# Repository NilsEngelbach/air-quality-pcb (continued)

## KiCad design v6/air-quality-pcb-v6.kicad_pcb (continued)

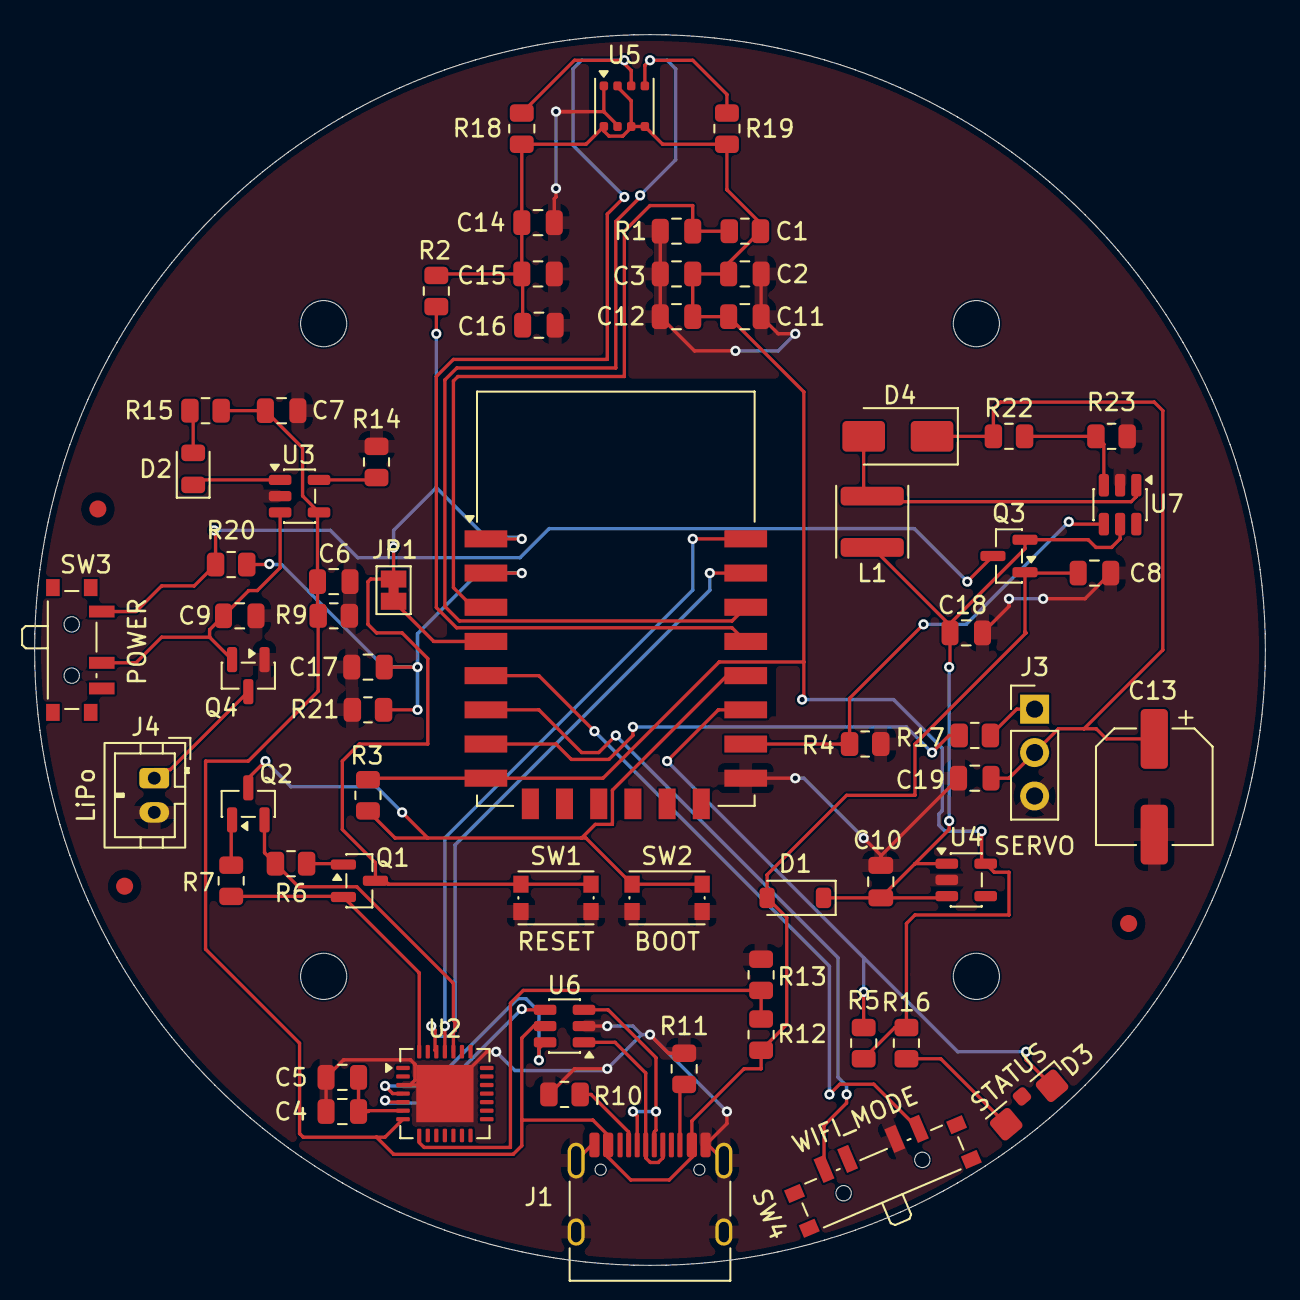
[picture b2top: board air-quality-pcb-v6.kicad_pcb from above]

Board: 2 copper layers, 72.0 x 72.0 mm, 72 parts (0 on the bottom side), 41 nets.

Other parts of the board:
FID1, FID2, FID3: Fiducial; Fiducial_1mm_Mask2mm
H1, H2, H3, H4: M2.5; MountingHole_2.7mm_M2.5

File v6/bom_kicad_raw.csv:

"Reference","Value","Footprint","Manufacturer","MPN","Description"
"C1","100nF","Capacitor_SMD:C_0805_2012Metric","Samsung Electro-Mechanics","CL21B104KBCNNNC","CAP CER 0.1UF 50V X7R 0805"
"C2","10uF","Capacitor_SMD:C_0805_2012Metric","YAGEO","CC0805KRX5R7BB106","CAP CER 10UF 16V X5R 0805"
"C3","100nF","Capacitor_SMD:C_0805_2012Metric","Samsung Electro-Mechanics","CL21B104KBCNNNC","CAP CER 0.1UF 50V X7R 0805"
"C4","4.7uF","Capacitor_SMD:C_0805_2012Metric","Samsung Electro-Mechanics","CL21A475KOFNNNG","CAP CER 4.7UF 16V X5R 0805"
"C5","100nF","Capacitor_SMD:C_0805_2012Metric","Samsung Electro-Mechanics","CL21B104KBCNNNC","CAP CER 0.1UF 50V X7R 0805"
"C6","4.7uF","Capacitor_SMD:C_0805_2012Metric","Samsung Electro-Mechanics","CL21A475KOFNNNG","CAP CER 4.7UF 16V X5R 0805"
"C7","4.7uF","Capacitor_SMD:C_0805_2012Metric","Samsung Electro-Mechanics","CL21A475KOFNNNG","CAP CER 4.7UF 16V X5R 0805"
"C8","100nF","Capacitor_SMD:C_0805_2012Metric","Samsung Electro-Mechanics","CL21B104KBCNNNC","CAP CER 0.1UF 50V X7R 0805"
"C9","4.7uF","Capacitor_SMD:C_0805_2012Metric","Samsung Electro-Mechanics","CL21A475KOFNNNG","CAP CER 4.7UF 16V X5R 0805"
"C10","1uF","Capacitor_SMD:C_0805_2012Metric","Samsung Electro-Mechanics","CL21B105KOFNNWE","CAP CER 1UF 16V X7R 0805"
"C11","10uF","Capacitor_SMD:C_0805_2012Metric","YAGEO","CC0805KRX5R7BB106","CAP CER 10UF 16V X5R 0805"
"C12","100nF","Capacitor_SMD:C_0805_2012Metric","Samsung Electro-Mechanics","CL21B104KBCNNNC","CAP CER 0.1UF 50V X7R 0805"
"C13","100uF","Capacitor_SMD:CP_Elec_6.3x5.4","Nichicon","UCD1C101MCL1GS","CAP ALUM 100UF 20% 16V SMD 6.3mm dia"
"C14","100nF","Capacitor_SMD:C_0805_2012Metric","Samsung Electro-Mechanics","CL21B104KBCNNNC","CAP CER 0.1UF 50V X7R 0805"
"C15","100nF","Capacitor_SMD:C_0805_2012Metric","Samsung Electro-Mechanics","CL21B104KBCNNNC","CAP CER 0.1UF 50V X7R 0805"
"C16","10uF","Capacitor_SMD:C_0805_2012Metric","YAGEO","CC0805KRX5R7BB106","CAP CER 10UF 16V X5R 0805"
"C17","100nF","Capacitor_SMD:C_0805_2012Metric","Samsung Electro-Mechanics","CL21B104KBCNNNC","CAP CER 0.1UF 50V X7R 0805"
"C18","10uF","Capacitor_SMD:C_0805_2012Metric","YAGEO","CC0805KRX5R7BB106","CAP CER 10UF 16V X5R 0805"
"C19","22uF","Capacitor_SMD:C_0805_2012Metric","Samsung Electro-Mechanics","CL21A226KOQNNNG","CAP CER 22UF 16V X5R 0805"
"D1","B5819W","Diode_SMD:D_SOD-123","MCC (Micro Commercial Components)","B5819W-TP","DIODE SCHOTTKY 40V 1A SOD-123"
"D2","CHG-GREEN","LED_SMD:LED_0805_2012Metric","Lite-On Inc.","LTST-C170GKT","LED GREEN CLEAR 0805 SMD"
"D3","STATUS","LED_SMD:LED_Kingbright_KPA-3010_3x2x1mm","Kingbright","KPA-3010QBC-D","LED BLUE CLEAR RIGHT ANGLE SMD 3.0x2.0x1.0mm side-view; status + WiFi setup feedback"
"D4","SS34","Diode_SMD:D_SMA","Comchip Technology","SS34-HF","DIODE SCHOTTKY 40V 3A DO-214AC (SMA)"
"J1","USB-C","Connector_USB:USB_C_Receptacle_HRO_TYPE-C-31-M-12","Korean Hroparts (HRO)","TYPE-C-31-M-12","USB Type-C 2.0 receptacle 16P mid-mount SMD"
"J3","SERVO","Connector_PinHeader_2.54mm:PinHeader_1x03_P2.54mm_Vertical","Wurth Elektronik","61300311121","CONN HEADER VERT 3POS 2.54MM THT"
"J4","LiPo","Connector_JST:JST_PH_B2B-PH-K_1x02_P2.00mm_Vertical","JST","B2B-PH-K-S","CONN HEADER VERT 2POS 2MM JST PH THT"
"JP1","DEEPSLEEP","Jumper:SolderJumper-2_P1.3mm_Bridged_Pad1.0x1.5mm","","",""
"L1","10uH","Inductor_SMD:L_Sunlord_SWPA4030S","Sunlord","SWPA4030S100MT","FIXED IND 10UH 1.5A 130 MOHM SMD 4x4x3"
"Q1","MMBT2222A","Package_TO_SOT_SMD:SOT-23","onsemi","MMBT2222ALT1G","TRANS NPN 40V 0.6A SOT-23"
"Q2","MMBT2222A","Package_TO_SOT_SMD:SOT-23","onsemi","MMBT2222ALT1G","TRANS NPN 40V 0.6A SOT-23"
"Q3","DMG2305UX","Package_TO_SOT_SMD:SOT-23","Diodes Incorporated","DMG2305UX-7","MOSFET P-CH 20V 4.2A SOT-23"
"Q4","DMG2305UX","Package_TO_SOT_SMD:SOT-23","Diodes Incorporated","DMG2305UX-7","MOSFET P-CH 20V 4.2A SOT-23"
"R1","10k","Resistor_SMD:R_0805_2012Metric","YAGEO","RC0805FR-0710KL","RES 10K OHM 1% 1/8W 0805"
"R2","10k","Resistor_SMD:R_0805_2012Metric","YAGEO","RC0805FR-0710KL","RES 10K OHM 1% 1/8W 0805"
"R3","10k","Resistor_SMD:R_0805_2012Metric","YAGEO","RC0805FR-0710KL","RES 10K OHM 1% 1/8W 0805"
"R4","10k","Resistor_SMD:R_0805_2012Metric","YAGEO","RC0805FR-0710KL","RES 10K OHM 1% 1/8W 0805"
"R5","10k","Resistor_SMD:R_0805_2012Metric","YAGEO","RC0805FR-0710KL","RES 10K OHM 1% 1/8W 0805"
"R6","10k","Resistor_SMD:R_0805_2012Metric","YAGEO","RC0805FR-0710KL","RES 10K OHM 1% 1/8W 0805"
"R7","10k","Resistor_SMD:R_0805_2012Metric","YAGEO","RC0805FR-0710KL","RES 10K OHM 1% 1/8W 0805"
"R9","100k","Resistor_SMD:R_0805_2012Metric","YAGEO","RC0805FR-07100KL","RES 100K OHM 1% 1/8W 0805"
"R10","5.1k","Resistor_SMD:R_0805_2012Metric","YAGEO","RC0805FR-075K1L","RES 5.1K OHM 1% 1/8W 0805"
"R11","5.1k","Resistor_SMD:R_0805_2012Metric","YAGEO","RC0805FR-075K1L","RES 5.1K OHM 1% 1/8W 0805"
"R12","22.1k","Resistor_SMD:R_0805_2012Metric","YAGEO","RC0805FR-0722K1L","RES 22.1K OHM 1% 1/8W 0805"
"R13","47.5k","Resistor_SMD:R_0805_2012Metric","YAGEO","RC0805FR-0747K5L","RES 47.5K OHM 1% 1/8W 0805"
"R14","2.2k","Resistor_SMD:R_0805_2012Metric","YAGEO","RC0805FR-072K2L","RES 2.2K OHM 1% 1/8W 0805"
"R15","1k","Resistor_SMD:R_0805_2012Metric","YAGEO","RC0805FR-071KL","RES 1K OHM 1% 1/8W 0805"
"R16","220R","Resistor_SMD:R_0805_2012Metric","YAGEO","RC0805FR-07220RL","RES 220 OHM 1% 1/8W 0805"
"R17","100R","Resistor_SMD:R_0805_2012Metric","YAGEO","RC0805FR-07100RL","RES 100 OHM 1% 1/8W 0805"
"R18","10k","Resistor_SMD:R_0805_2012Metric","YAGEO","RC0805FR-0710KL","RES 10K OHM 1% 1/8W 0805"
"R19","10k","Resistor_SMD:R_0805_2012Metric","YAGEO","RC0805FR-0710KL","RES 10K OHM 1% 1/8W 0805"
"R20","1M","Resistor_SMD:R_0805_2012Metric","YAGEO","RC0805FR-071ML","RES 1M OHM 1% 1/8W 0805"
"R21","270k","Resistor_SMD:R_0805_2012Metric","YAGEO","RC0805FR-07270KL","RES 270K OHM 1% 1/8W 0805"
"R22","82k","Resistor_SMD:R_0805_2012Metric","YAGEO","RC0805FR-0782KL","RES 82K OHM 1% 1/8W 0805"
"R23","11k","Resistor_SMD:R_0805_2012Metric","YAGEO","RC0805FR-0711KL","RES 11K OHM 1% 1/8W 0805"
"SW1","RESET","Button_Switch_SMD:SW_Push_1P1T_NO_CK_KMR2","C&K","KMR221G LFS","SWITCH TACTILE SPST-NO 0.05A 32V SMD"
"SW2","BOOT","Button_Switch_SMD:SW_Push_1P1T_NO_CK_KMR2","C&K","KMR221G LFS","SWITCH TACTILE SPST-NO 0.05A 32V SMD"
"SW3","POWER","Button_Switch_SMD:SW_SPDT_PCM12","C&K","PCM12SMTBR","SWITCH SLIDE SPDT 0.3A 6V SMD right-angle"
"SW4","WIFI_MODE","Button_Switch_SMD:SW_SP3T_PCM13","C&K","PCM13SMTR","SWITCH SLIDE SP3T ON-ON-ON 0.3A 6V SMD right-angle; WiFi mode select (OFF/SPARSE/CONTINUOUS)"
"U1","ESP-12F","RF_Module:ESP-12E","Ai-Thinker","ESP-12F","ESP8266 WiFi module ESP-12F"
"U2","CP2102N-A02-GQFN28","Package_DFN_QFN:QFN-28-1EP_5x5mm_P0.5mm_EP3.35x3.35mm","Silicon Labs","CP2102N-A02-GQFN28","IC USB TO UART BRIDGE QFN-28"
"U3","MCP73831","Package_TO_SOT_SMD:SOT-23-5","Microchip Technology","MCP73831T-2ACI/OT","IC BATT CNTL LI-ION 1CEL SOT-23-5"
"U4","AP2112K-3.3","Package_TO_SOT_SMD:SOT-23-5","Diodes Incorporated","AP2112K-3.3TRG1","IC REG LINEAR 3.3V 600MA SOT-23-5"
"U5","BME688","Package_LGA:Bosch_LGA-8_3x3mm_P0.8mm_ClockwisePinNumbering","Bosch Sensortec","BME688","SENSOR GAS/HUM/PRES/TEMP I2C LGA-8"
"U6","USBLC6-2SC6","Package_TO_SOT_SMD:SOT-23-6","STMicroelectronics","USBLC6-2SC6","TVS DIODE 5.25VWM 17VC SOT-23-6"
"U7","MT3608","Package_TO_SOT_SMD:SOT-23-6","Aerosemi Tech","MT3608","IC BOOST CONVERTER ADJ 1.2A SOT-23-6"
